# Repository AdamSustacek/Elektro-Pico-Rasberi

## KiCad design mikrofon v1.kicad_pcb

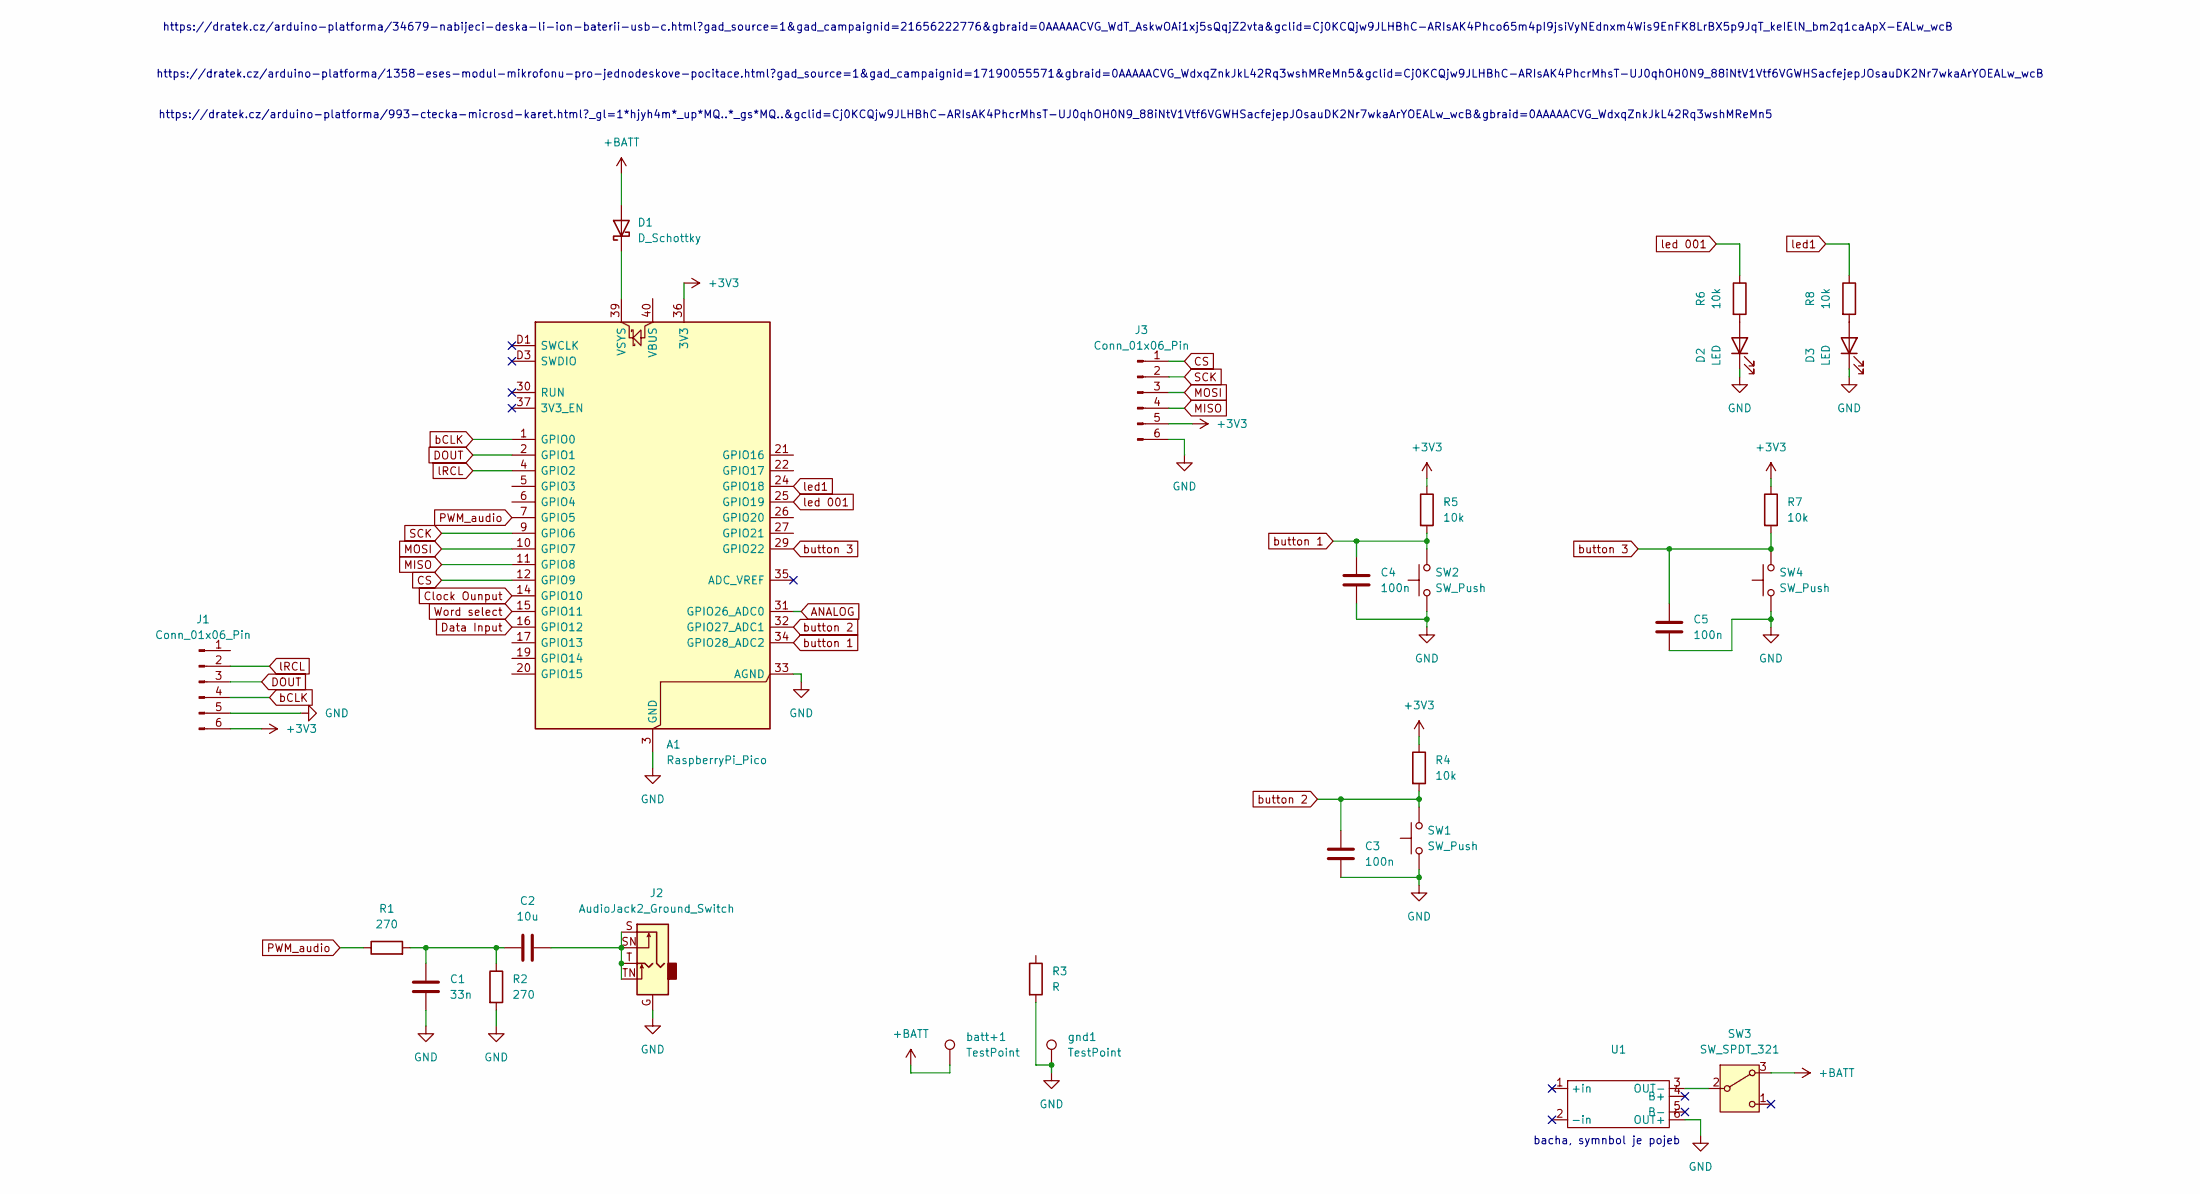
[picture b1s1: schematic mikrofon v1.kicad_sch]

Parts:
A1: RaspberryPi_Pico; RaspberryPi_Pico_SMD_HandSolder
C1: 33n; C_0805_2012Metric_Pad1.18x1.45mm_HandSolder
C2: 10u; C_0805_2012Metric_Pad1.18x1.45mm_HandSolder
C3, C4, C5: 100n; C_0805_2012Metric_Pad1.18x1.45mm_HandSolder
D1: D_Schottky; D_SMA
D2, D3: LED; LED_0805_2012Metric
J1, J3: Conn_01x06_Pin; PinHeader_1x06_P2.54mm_Vertical
J2: AudioJack2_Ground_Switch; Jack_3.5mm_CUI_SJ1-3525N_Horizontal
R1, R2: 270; R_0805_2012Metric_Pad1.20x1.40mm_HandSolder
R3: R; R_0603_1608Metric
R4, R5, R6, R7, R8: 10k; R_0805_2012Metric_Pad1.20x1.40mm_HandSolder
SW1, SW2, SW4: SW_Push; SW_PUSH_6mm_H4.3mm
SW3: SW_SPDT_321; SW_Slide_SPDT_Straight_CK_OS102011MS2Q
U1: Untitled
batt+1: TestPoint; Pin_D1.2mm_L11.3mm_W3.0mm_Flat
gnd1: TestPoint; Pin_D1.2mm_L11.3mm_W3.0mm_Flat

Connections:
+3V3: A1.36 (3V3), J1.6, J3.5, R4.1, R5.1, R7.1
+BATT: D1.2 (A), SW3.3 (A), batt+1.1
ANALOG: A1.31 (GPIO26_ADC0)
CS: A1.12 (GPIO9), J3.1
Clock Ounput: A1.14 (GPIO10)
DOUT: A1.2 (GPIO1), J1.3
Data Input: A1.16 (GPIO12)
GND: A1.3 (GND), A1.8 (GND), A1.13 (GND), A1.18 (GND), A1.23 (GND), A1.28 (GND), A1.33 (AGND), A1.38 (GND), A1.D2 (GND), C1.1, C3.1, C4.1, C5.1, D2.1 (K), D3.1 (K), J1.5, J2.G, J3.6, R2.2, R3.2, SW1.1, SW2.1, SW4.1, U1.6 (OUT+), gnd1.1
MISO: A1.11 (GPIO8), J3.4
MOSI: A1.10 (GPIO7), J3.3
unnamed: A1.39 (VSYS), D1.1 (K)
unnamed: C1.2, C2.2, R1.2, R2.1
unnamed: C2.1, J2.S, J2.SN, J2.T, J2.TN
unnamed: D2.2 (A), R6.2
unnamed: D3.2 (A), R8.2
unnamed: SW3.2 (B), U1.3 (OUT-)
PWM_audio: A1.7 (GPIO5), R1.1
SCK: A1.9 (GPIO6), J3.2
Word select: A1.15 (GPIO11)
bCLK: A1.1 (GPIO0), J1.4
button 1: A1.34 (GPIO28_ADC2), C4.2, R5.2, SW2.2
button 2: A1.32 (GPIO27_ADC1), C3.2, R4.2, SW1.2
button 3: A1.29 (GPIO22), C5.2, R7.2, SW4.2
lRCL: A1.4 (GPIO2), J1.2
led1: A1.24 (GPIO18), R8.1
led 001: A1.25 (GPIO19), R6.1

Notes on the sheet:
https://dratek.cz/arduino-platforma/1358-eses-modul-mikrofonu-pro-jednodeskove-pocitace.html?gad_source=1&gad_campaignid=17190055571&gbraid=0AAAAACVG_WdxqZnkJkL42Rq3wshMReMn5&gclid=Cj0KCQjw9JLHBhC-ARIsAK4PhcrMhsT-UJ0qhOH0N9_88iNtV1Vtf6VGWHSacfejepJOsauDK2Nr7wkaArYOEALw_wcB
bacha, symnbol je pojeb
https://dratek.cz/arduino-platforma/993-ctecka-microsd-karet.html?_gl=1*hjyh4m*_up*MQ..*_gs*MQ..&gclid=Cj0KCQjw9JLHBhC-ARIsAK4PhcrMhsT-UJ0qhOH0N9_88iNtV1Vtf6VGWHSacfejepJOsauDK2Nr7wkaArYOEALw_wcB&gbraid=0AAAAACVG_WdxqZnkJkL42Rq3wshMReMn5
https://dratek.cz/arduino-platforma/34679-nabijeci-deska-li-ion-baterii-usb-c.html?gad_source=1&gad_campaignid=21656222776&gbraid=0AAAAACVG_WdT_AskwOAi1xj5sQqjZ2vta&gclid=Cj0KCQjw9JLHBhC-ARIsAK4Phco65m4pI9jsiVyNEdnxm4Wis9EnFK8LrBX5p9JqT_keIElN_bm2q1caApX-EALw_wcB

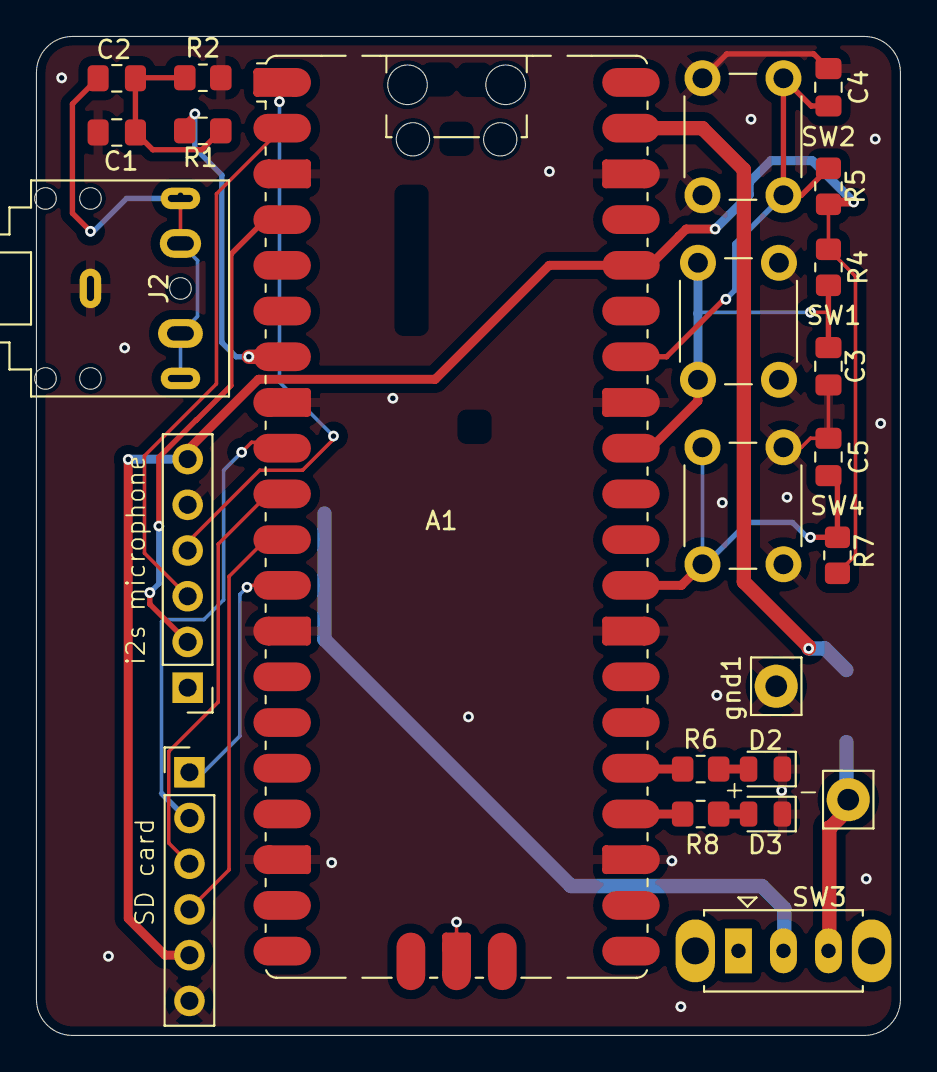
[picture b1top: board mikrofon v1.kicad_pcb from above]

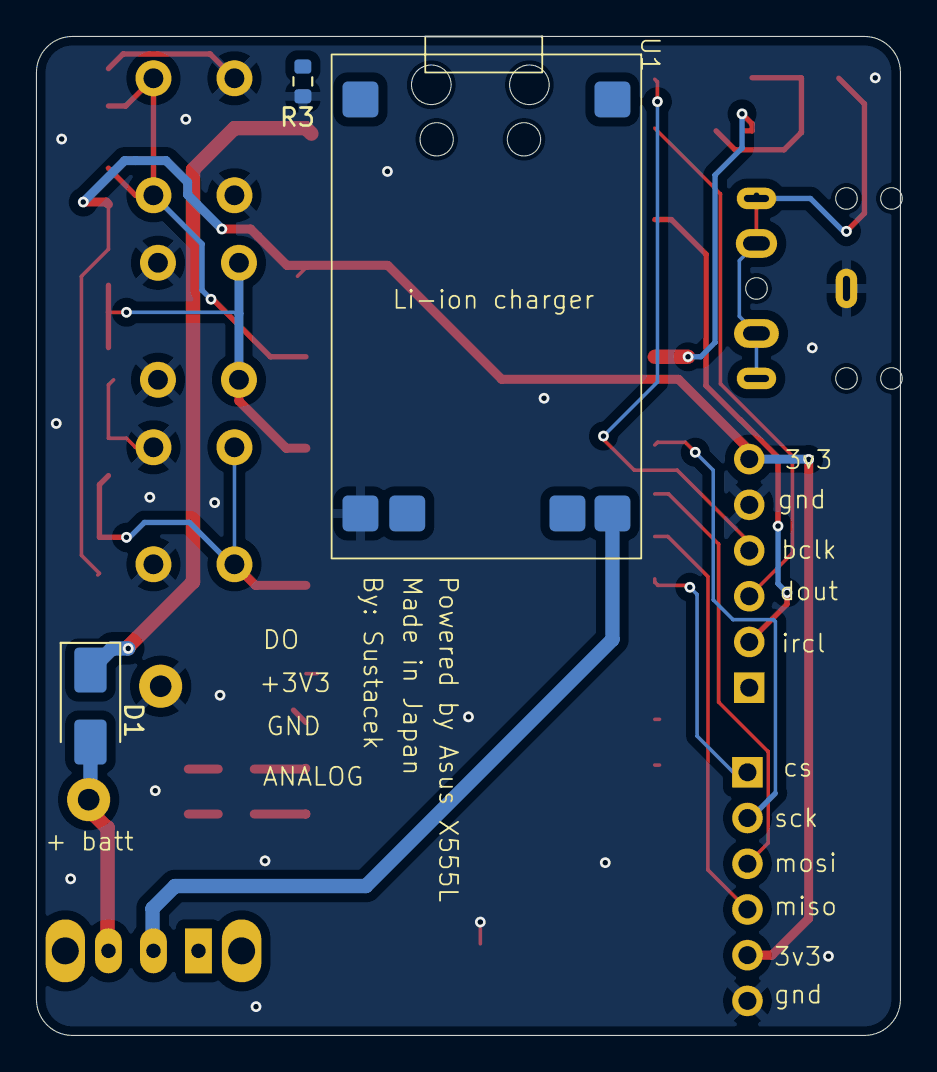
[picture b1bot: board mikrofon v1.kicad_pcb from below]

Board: 2 copper layers, 48.0 x 55.5 mm, 27 parts (3 on the bottom side), 22 nets.
